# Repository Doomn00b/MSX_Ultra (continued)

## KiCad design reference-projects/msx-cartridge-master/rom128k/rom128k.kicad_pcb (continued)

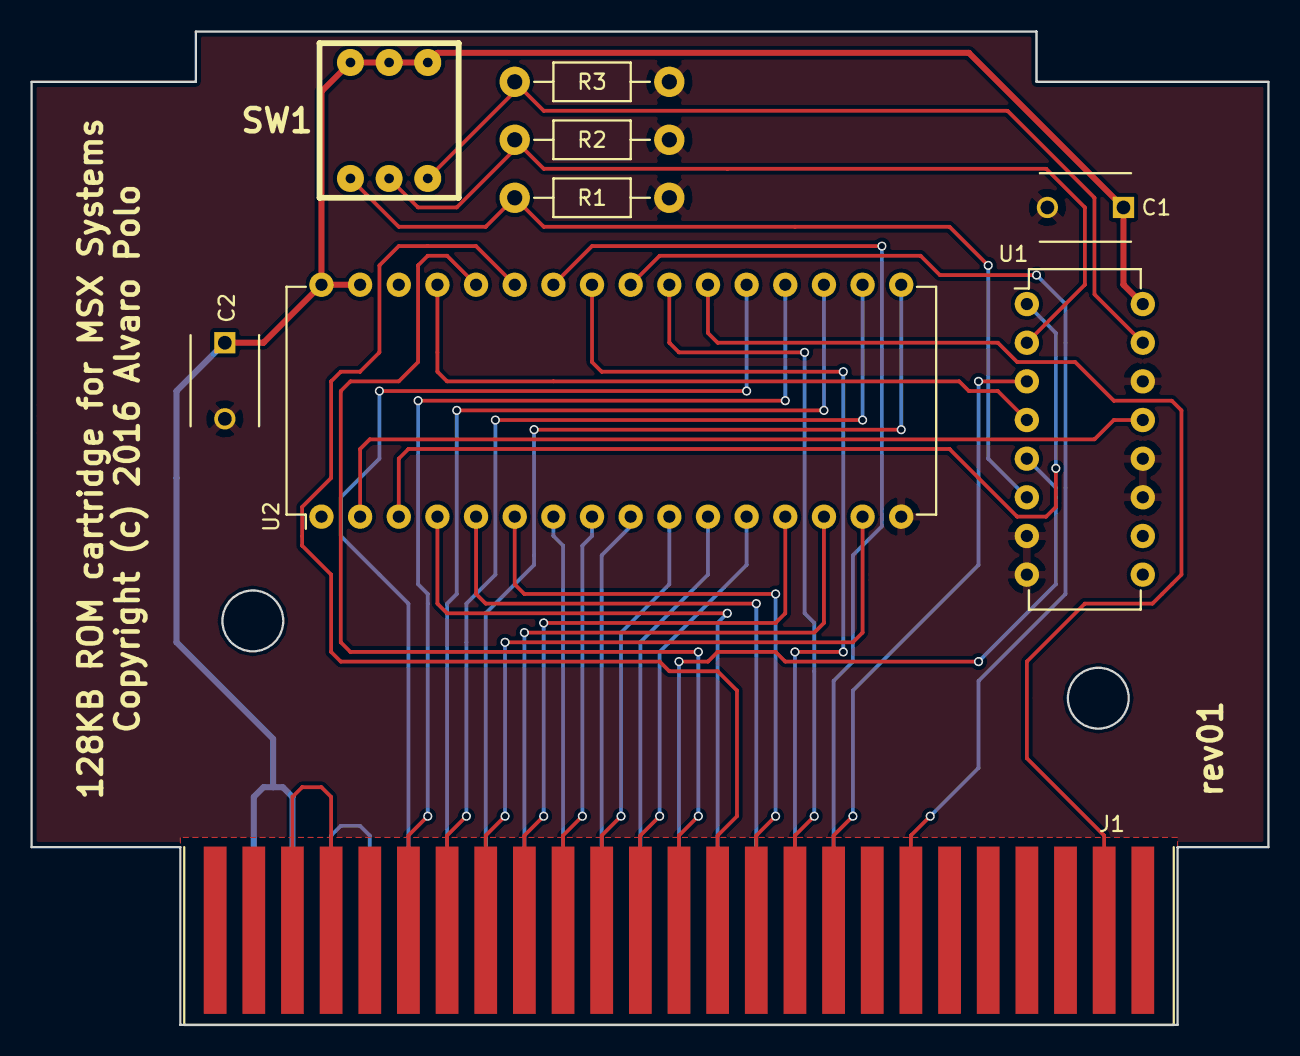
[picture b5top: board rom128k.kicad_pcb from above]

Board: 2 copper layers, 81.3 x 65.3 mm, 9 parts (0 on the bottom side), 35 nets.

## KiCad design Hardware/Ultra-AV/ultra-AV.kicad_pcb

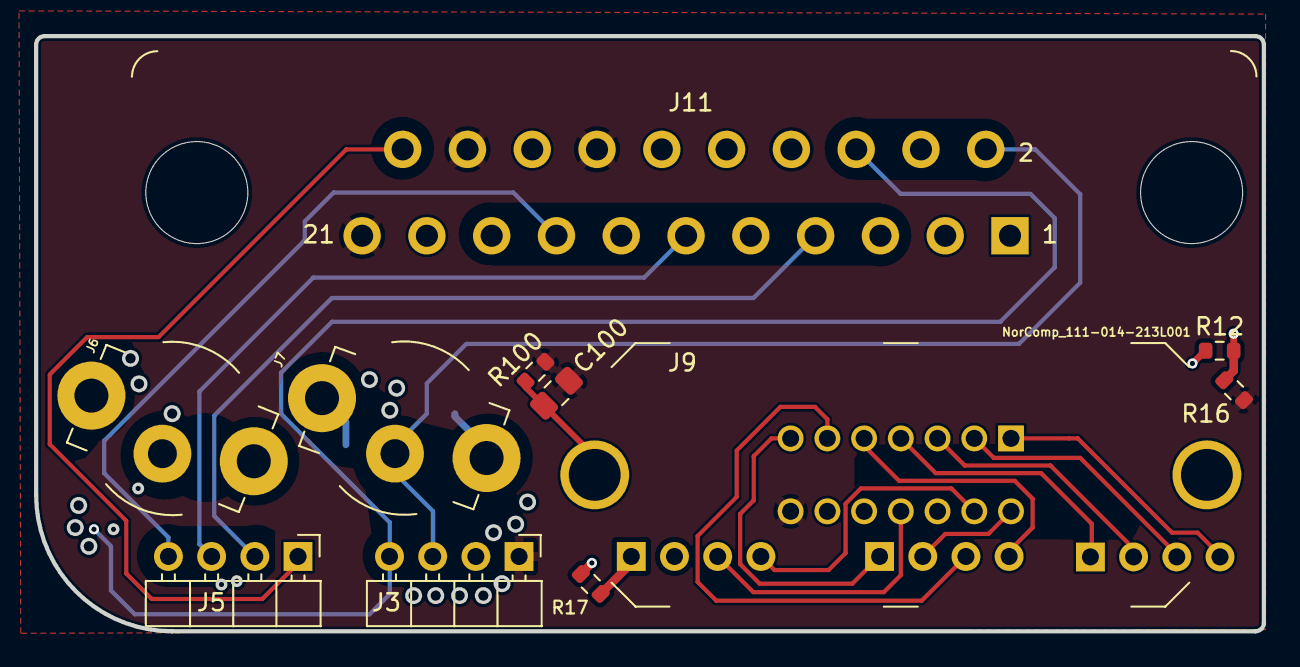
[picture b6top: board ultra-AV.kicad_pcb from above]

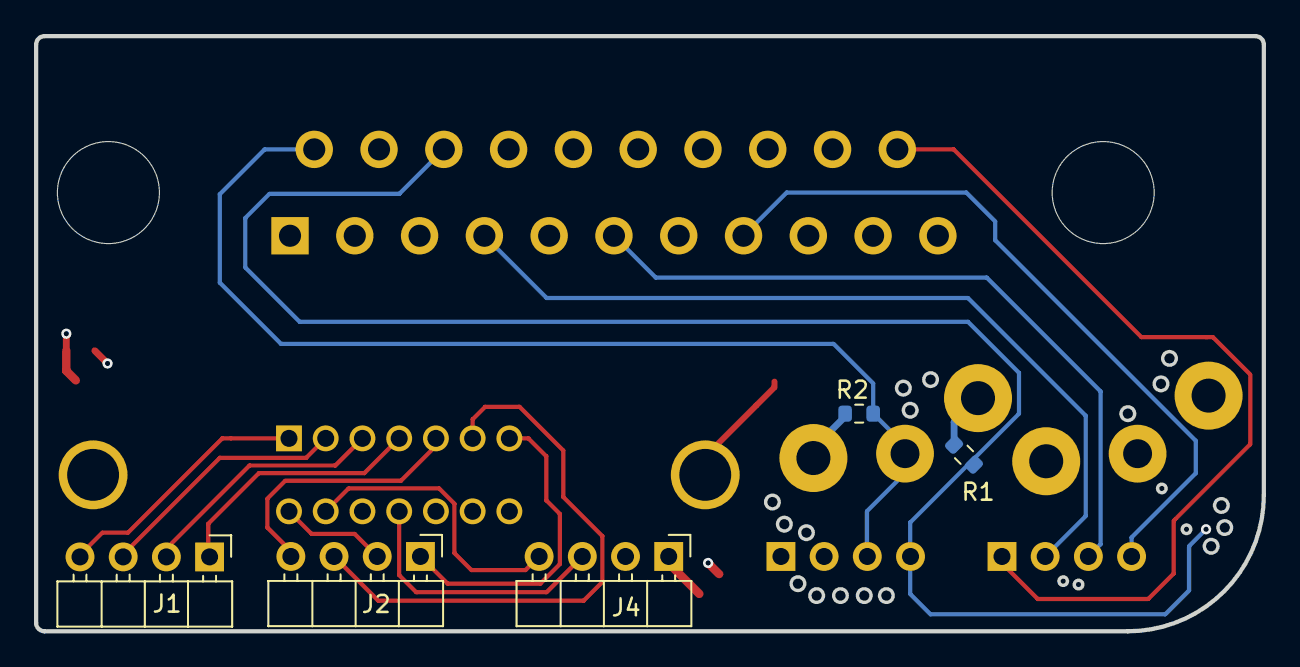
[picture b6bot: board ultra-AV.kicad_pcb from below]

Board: 4 copper layers, 72.2 x 35.0 mm, 16 parts (5 on the bottom side), 23 nets.

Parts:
C100: C_CL21B105KBFNNNF; C_0805_2012Metric_Pad1.18x1.45mm_HandSolder
J1, J2, J3, J4, J5: Conn_01x04; PinHeader_1x04_P2.54mm_Horizontal_less-silk
J6: Conn_RCJ-023; CUI_RCJ-023
J7: Conn_RCJ-022; CUI_RCJ-022
J9: NorComp_111-014-213L001; Conn_Micro_Ribbon_14F_Vertical
J11: TC_1578891_SCART; SCART-21_Female_Vertical_P1.905x2.54mm_EdgePinOffset10.7mm
R1, R2: 47k; R_0603_1608Metric
R12, R16: 100; R_0603_1608Metric
R17: 1k; R_0603_1608Metric
R100: R_ERJ-3GEYJ105V; R_0603_1608Metric

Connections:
+5V: J4.2, R12.1
+12V: J4.1, R17.2
/2.5V: J11.16 (BLNK), R12.2, R16.1
/+12V-1K: J11.8 (SW), R17.1
/AUD_L: J3.4, J6.2 (IN2), J11.6 (AIL/MONO), R1.1
/AUD_R: J3.3, J7.2 (IN2), J11.2 (AIR), R2.2
/BOUT: J5.2, J11.7 (BLUE)
/CSYNC: J5.1, J11.20 (VIDIN/Sync)
/GOUT: J5.3, J11.11 (GREEN)
/PD0: J1.3, J9.2
/PD1: J1.2, J9.3
/PD2: J1.1, J9.4
/PD3: J2.4, J9.5
/PD4: J2.3, J9.6
/PD5: J2.1, J9.7
/PD6: J2.2, J9.8
/PD7: J4.4, J9.9
/PRT_BUSY: J4.3, J9.11
/ROUT: J5.4, J11.15 (RED/CHROMA)
/~STROBE: J1.4, J9.1
GND: C100.2, J3.1, J9.14, J11.14 (DATGND), J11.18 (BLNKGND), J11.21 (SH), R16.2, R100.1
GNDA: J3.2, J6.1A (IN1), J6.1B (IN1), J7.1A (IN1), J7.1B (IN1), J11.4 (AUGND), J11.5 (BGND), J11.9 (GGND), J11.13 (RGND), J11.17 (VGND), R1.2, R2.1
unnamed: C100.1, J9.15 (SH), R100.2

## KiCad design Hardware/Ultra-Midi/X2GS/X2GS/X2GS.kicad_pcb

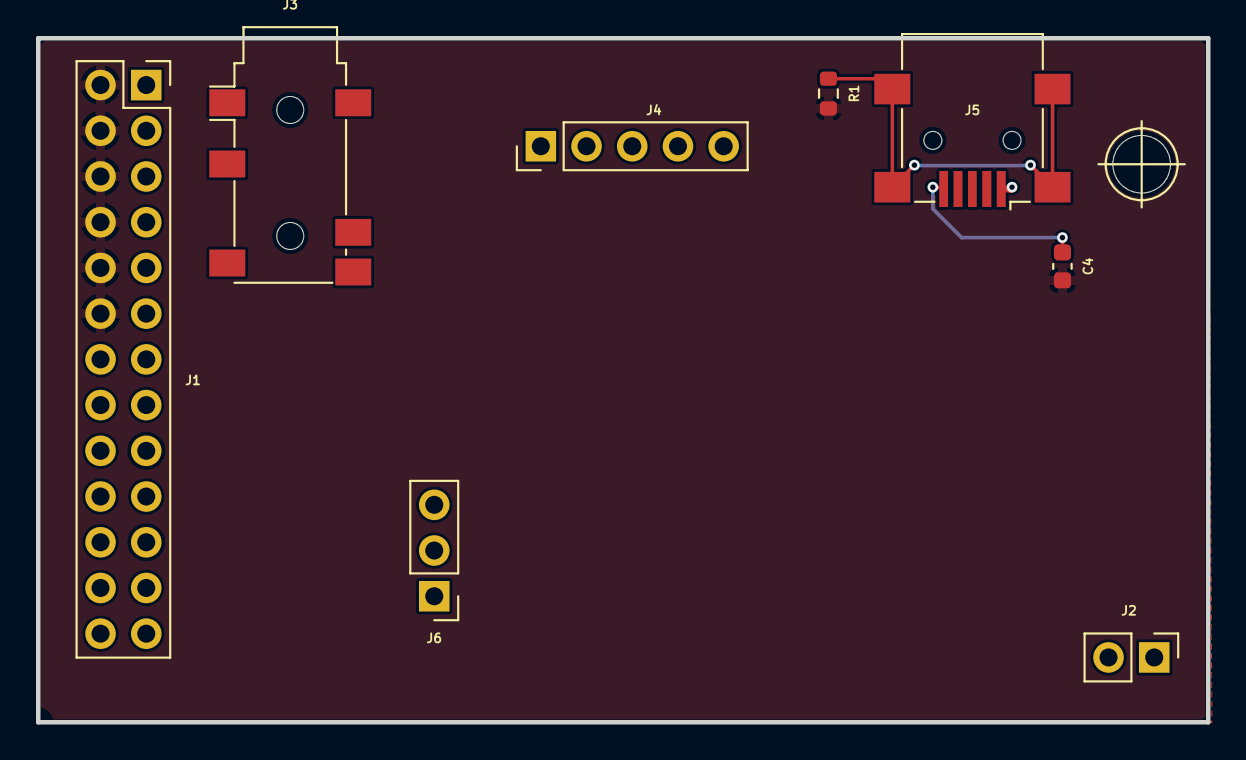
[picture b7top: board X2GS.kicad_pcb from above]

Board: 4 copper layers, 65.0 x 38.0 mm, 9 parts (0 on the bottom side), 6 nets.

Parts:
C4: C_GRM188D71A106KA73D; C_0603_1608Metric
H1: MountingHole; MountingHole_3.2mm_M3
J1: Waveblaster_header_02x13; PinSocket_2x13_P2.54mm_Vertical
J2: Conn_01x02; PinHeader_1x02_P2.54mm_Vertical
J3: AudioJack5_Ground; Jack_3.5mm_PJ311_Horizontal
J4: Conn_01x05; PinHeader_1x05_P2.54mm_Vertical
J5: USB_B_Mini; USB_Mini-B_Lumberg_2486_01_Horizontal
J6: Conn_01x03; PinHeader_1x03_P2.54mm_Vertical
R1: 1M; R_0603_1608Metric

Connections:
+5V: J1.5 (+5V), J1.9 (+5V), J1.13 (+5V), J5.1 (VBUS)
+12V: J1.17 (+12V), J1.21 (+12V)
GNDA: J1.16 (GND), J1.18 (GND), J1.20 (GND), J1.22 (GND), J1.24 (GND), J1.26 (GND)
GNDD: C4.2, J1.2 (GND), J1.4 (GND), J1.6 (GND), J1.8 (GND), J1.10 (GND), J1.12 (GND), R1.2
unnamed: C4.1, J5.5 (GND)
unnamed: J5.6 (Shield), R1.1

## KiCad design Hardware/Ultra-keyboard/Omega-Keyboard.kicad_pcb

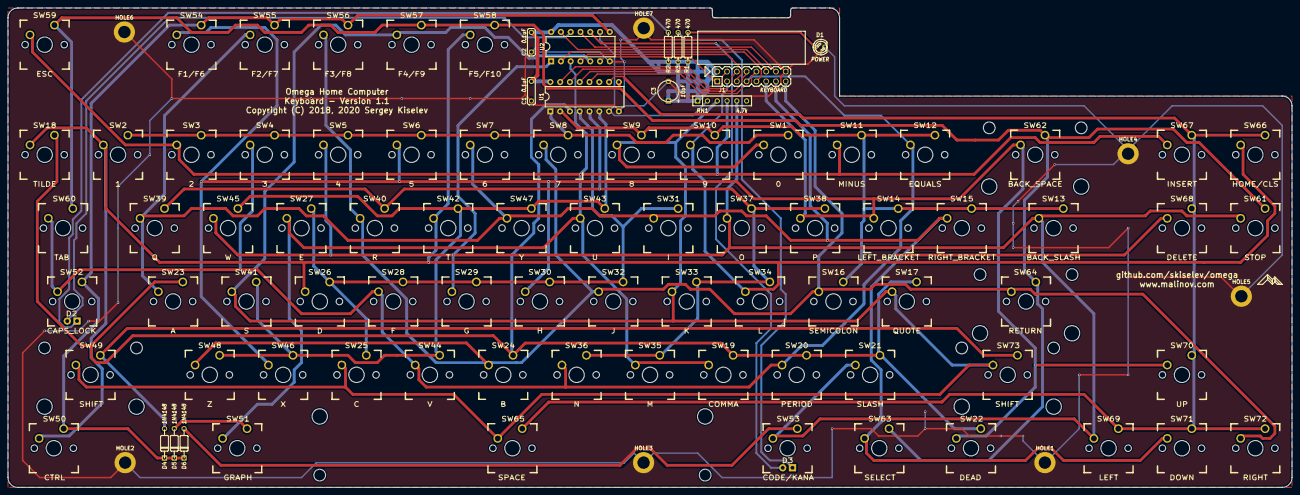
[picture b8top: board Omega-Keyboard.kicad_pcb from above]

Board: 2 copper layers, 333.4 x 124.5 mm, 96 parts (0 on the bottom side), 37 nets.

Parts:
C1, C2: 0.1uF; Cap_Cer_508
C3: 10uF; Cap_Tant_508
D1: POWER; LED_3mm
D2: CAPS; CHERRY_MX_LED
D3: KANA; CHERRY_MX_LED
D4, D5, D6: 1N4148; Diode_762
HOLE1, HOLE2, HOLE3, HOLE4, HOLE5, HOLE6, HOLE7: MountingHole_Pad; MountingHole_3.2mm_M3_ISO14580_Pad
J1: KEYBOARD; Conn_Pin_Header_8x2_2.54mm
R1, R2, R3: 470; Res_762
RN1: 4.7k; Conn_SIL6
SW1: 0; CHERRY_PCB_100H
SW2: 1; CHERRY_PCB_100H
SW3: 2; CHERRY_PCB_100H
SW4: 3; CHERRY_PCB_100H
SW5: 4; CHERRY_PCB_100H
SW6: 5; CHERRY_PCB_100H
SW7: 6; CHERRY_PCB_100H
SW8: 7; CHERRY_PCB_100H
SW9: 8; CHERRY_PCB_100H
SW10: 9; CHERRY_PCB_100H
SW11: MINUS; CHERRY_PCB_100H
SW12: EQUALS; CHERRY_PCB_100H
SW13: BACK_SLASH; CHERRY_PCB_150H
SW14: LEFT_BRACKET; CHERRY_PCB_100H
SW15: RIGHT_BRACKET; CHERRY_PCB_100H
SW16: SEMICOLON; CHERRY_PCB_100H
SW17: QUOTE; CHERRY_PCB_100H
SW18: TILDE; CHERRY_PCB_100H
SW19: COMMA; CHERRY_PCB_100H
SW20: PERIOD; CHERRY_PCB_100H
SW21: SLASH; CHERRY_PCB_100H
SW22: DEAD; CHERRY_PCB_125H
SW23: A; CHERRY_PCB_100H
SW24: B; CHERRY_PCB_100H
SW25: C; CHERRY_PCB_100H
SW26: D; CHERRY_PCB_100H
SW27: E; CHERRY_PCB_100H
SW28: F; CHERRY_PCB_100H
SW29: G; CHERRY_PCB_100H
SW30: H; CHERRY_PCB_100H
SW31: I; CHERRY_PCB_100H
SW32: J; CHERRY_PCB_100H
SW33: K; CHERRY_PCB_100H
SW34: L; CHERRY_PCB_100H
SW35: M; CHERRY_PCB_100H
SW36: N; CHERRY_PCB_100H
SW37: O; CHERRY_PCB_100H
SW38: P; CHERRY_PCB_100H
SW39: Q; CHERRY_PCB_100H
SW40: R; CHERRY_PCB_100H
SW41: S; CHERRY_PCB_100H
SW42: T; CHERRY_PCB_100H
SW43: U; CHERRY_PCB_100H
SW44: V; CHERRY_PCB_100H
SW45: W; CHERRY_PCB_100H
SW46: X; CHERRY_PCB_100H
SW47: Y; CHERRY_PCB_100H
SW48: Z; CHERRY_PCB_100H
SW49: SHIFT; CHERRY_PCB_225H
SW50: CTRL; CHERRY_PCB_125H
SW51: GRAPH; CHERRY_PCB_125H
SW52: CAPS_LOCK; CHERRY_PCB_175H
SW53: CODE/KANA; CHERRY_PCB_125H
SW54: F1/F6; CHERRY_PCB_100H
SW55: F2/F7; CHERRY_PCB_100H
SW56: F3/F8; CHERRY_PCB_100H
SW57: F4/F9; CHERRY_PCB_100H
SW58: F5/F10; CHERRY_PCB_100H
SW59: ESC; CHERRY_PCB_100H
SW60: TAB; CHERRY_PCB_150H
SW61: STOP; CHERRY_PCB_100H
SW62: BACK_SPACE; CHERRY_PCB_200H
SW63: SELECT; CHERRY_PCB_125H
SW64: RETURN; CHERRY_PCB_225H
SW65: SPACE; CHERRY_PCB_625H
SW66: HOME/CLS; CHERRY_PCB_100H
SW67: INSERT; CHERRY_PCB_100H
SW68: DELETE; CHERRY_PCB_100H
SW69: LEFT; CHERRY_PCB_100H
SW70: UP; CHERRY_PCB_100H
SW71: DOWN; CHERRY_PCB_100H
SW72: RIGHT; CHERRY_PCB_100H
SW73: SHIFT; CHERRY_PCB_275H
U1: 74LS145; DIP-16_W7.62mm
U2: 74LS07; DIP-14_W7.62mm

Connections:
/CAPS_LED: J1.12, U2.13
/CAPS_LED_BUFFERED: D2.1, U2.12
/CODE: D6.2, SW53.1
/COLUMN0: RN1.3, SW1.2, SW9.2, SW17.2, SW25.2, SW33.2, SW41.2, SW49.2, SW57.2, SW65.2, SW73.2, U2.5
/COLUMN0_BUF: J1.1, U2.6
/COLUMN1: J1.3, SW2.2, SW10.2, SW18.2, SW26.2, SW34.2, SW42.2, SW50.2, SW58.2, SW66.2
/COLUMN2: RN1.4, SW3.2, SW11.2, SW19.2, SW27.2, SW35.2, SW43.2, SW51.2, SW59.2, SW67.2, U2.3
/COLUMN2_BUF: J1.5, U2.4
/COLUMN3: J1.7, SW4.2, SW12.2, SW20.2, SW28.2, SW36.2, SW44.2, SW52.2, SW60.2, SW68.2
/COLUMN4: RN1.5, SW5.2, SW13.2, SW21.2, SW29.2, SW37.2, SW45.2, SW53.2, SW61.2, SW69.2, U2.1
/COLUMN4_BUF: J1.9, U2.2
/COLUMN5: J1.11, SW6.2, SW14.2, SW22.2, SW30.2, SW38.2, SW46.2, SW54.2, SW62.2, SW70.2
/COLUMN6: J1.13, SW7.2, SW15.2, SW23.2, SW31.2, SW39.2, SW47.2, SW55.2, SW63.2, SW71.2
/COLUMN7: J1.15, SW8.2, SW16.2, SW24.2, SW32.2, SW40.2, SW48.2, SW56.2, SW64.2, SW72.2
/D1+: D1.2, R1.2
/D2+: D2.2, R2.2
/D3+: D3.2, R3.2
/GRAPH: D5.2, SW51.1
/KANA_LED: J1.14, U2.11
/KANA_LED_BUFFERED: D3.1, U2.10
/ROW0: SW1.1, SW2.1, SW3.1, SW4.1, SW5.1, SW6.1, SW7.1, SW8.1, U1.1
/ROW1: SW9.1, SW10.1, SW11.1, SW12.1, SW13.1, SW14.1, SW15.1, SW16.1, U1.2
/ROW2: SW17.1, SW18.1, SW19.1, SW20.1, SW21.1, SW22.1, SW23.1, SW24.1, U1.3
/ROW3: SW25.1, SW26.1, SW27.1, SW28.1, SW29.1, SW30.1, SW31.1, SW32.1, U1.4
/ROW4: SW33.1, SW34.1, SW35.1, SW36.1, SW37.1, SW38.1, SW39.1, SW40.1, U1.5
/ROW5: SW41.1, SW42.1, SW43.1, SW44.1, SW45.1, SW46.1, SW47.1, SW48.1, U1.6
/ROW6: D4.1, D5.1, D6.1, SW50.1, SW52.1, SW54.1, SW55.1, SW56.1, U2.8
/ROW6_UNBUF: RN1.2, U1.7, U2.9
/ROW7: SW57.1, SW58.1, SW59.1, SW60.1, SW61.1, SW62.1, SW63.1, SW64.1, U1.9
/ROW8: SW65.1, SW66.1, SW67.1, SW68.1, SW69.1, SW70.1, SW71.1, SW72.1, U1.10
/ROW_A: J1.4, U1.15
/ROW_B: J1.6, U1.14
/ROW_C: J1.8, U1.13
/ROW_D: J1.10, U1.12
/SHIFT: D4.2, SW49.1, SW73.1
GND: C1.2, C2.2, C3.2, D1.1, HOLE1.1, HOLE2.1, HOLE3.1, HOLE4.1, HOLE5.1, HOLE6.1, HOLE7.1, J1.16, U1.8, U2.7
VCC: C1.1, C2.1, C3.1, J1.2, R1.1, R2.1, R3.1, RN1.1, U1.16, U2.14

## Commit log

2022-05-06 Initial commit.
    Setting up folder-structure, and uploading the currently achieved progress.
2022-05-29 Routed the VDP-board further, as well as making it a 4-layer board - also added an exception in the gitignore, for big images.
2022-06-10 Finished the VDP-board, finished up the mixer-section, removed the buffer-pins from the FPGA, and instead added external buffers for the slots, designed a marquee-block with the Ultra-MSX logo, desig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
2022-06-11 Started routing the Cassette-player on the PCB.
2022-06-26 Added SD-card slot, made basic 3d-model for sd-card slot, connected it up in the schematic, and numerous other tweaks.
2022-07-19 Redesigned VDP-board to include a socket, increased it to 4 layers. Various clean-ups here and there. Improved the printer-port and joystick-port 3D-models. Improved the cooling-fin 3D-model, and add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
2022-07-19 Generated first PDF-files
2022-08-05 Reworked the Printer-port 3D model, and the Scart 3D-model. Generated a 3D model of the main board. Moved peripheral components from separate expansion-headers, to a singular IO-shield board.
2022-08-11 Redesigning of the IO-shield, to make room for Keyboard, power and USB.
2022-08-28 Started remodelling the MSX cart-shells, as they don't seem to fit the cartridge-pcb's. Bit of clean-up in the directories.
2022-09-12 slight bit of cleanup of folders and some work on 3D-models
2022-10-10 Multiple redesigns of the IO-shield. Replaced FPGA with lower pin-count AT10K, since the higher pin-count one is now obsolete.
2022-12-10 Added cooler and CPU-mount footprints, as well as Indication LEDs.
2023-04-27 Started fixing many small issues.
2023-10-12 Updated the readme, silenced multiple errors in Kicad regarding simulation-files.
2023-10-25 Added a 3D-model for the SDRAM-module. Prepping the design for a fork using a single, more modern FPGA.
2023-12-13 Many tweaks and changes, such as a slight redesign of the VDP-baord.
2023-12-13 Returned to Simm-72 memory module to simplify design, returned to AT40K40 with 254 io, FPGA.
